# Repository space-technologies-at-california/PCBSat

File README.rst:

=============
PCB Satellite
=============
Space Technologies at Cal (https://stac.berkeley.edu)

University of California, Berkeley

Getting Started
===============
Clone this repository. Then:

Eagle
-----
#. Obtain the `STAC Eagle library <https://github.com/space-technologies-at-california/electronics>`_ by running::
   
    git submodule init
    git submodule update

#. `Add the library to Eagle <https://www.instructables.com/id/Adding-a-Library-to-Eagle-CAD/>`_.

Firmware
--------
#. Install `MSP430-GCC <http://www.ti.com/tool/msp430-gcc-opensource>`_ and
   `MSPDebug <https://dlbeer.co.nz/mspdebug/>`_.

#. In *firmware/*, make a new file called *msp430.mk.inc* and specify the path
   to your MSP430-GCC installation. For example::

    MSP430_TOOLCHAIN=/usr/local/gcc-msp430-ti-toolchain-5.01.02.00

#. Run ``make`` from *firmware/* to build all firmware configurations. To
   build a specific configuration, change to the appropriate subdirectory (for
   example, *debug/*) and run ``make``. If ``make`` complains about a missing
   *gitrev.h*, type ``make gitrev.h`` and re-run.

#. To change a build configuration, edit *config.h* in the appropriate
   subdirectory.

Programming
~~~~~~~~~~~
#. Obtain a programmer. We use the MSP430F5529 LaunchPad to program our sprite
   using Spy-Bi-Wire (SBW), but any SBW-compatible programmer should work.

#. Disconnect the 5V, 3V, GND, SBW RST and TST jumpers from the LaunchPad.

#. Connect the 3V, GND, SBW RST and TST jumpers on the ezFET-lite side to the
   target.

#. Run ``make prog`` to program, and run ``make verify`` to read back what was
   programmed.

Simulation
----------
Dependencies: igrf12 (https://github.com/scivision/igrf12)

#. Run ``python3 pull_iss_locdata.py``. This will collect (timestamp, latitude,longitude) data of the ISS for 9 hours at 10 second increments. This will create an output file in the current directory titled ``iss_loc_data_{timestamp}.csv``.  
#. Run ``python3 data_gen.py -f iss_loc_data_{timestamp}.csv`` where timestamp corresponds to the file created in the previous step. This will create an output file in the current directory that contains magnetometer data (x,y,z), gyrometer data (x,y,z), and the expected axis and power that the PCBSat should rotate along in addition to the file's previous contents. This output file will be titled ``full_{timestamp}.csv``. The units for the magnetometer data are Gauss and the units for the gyrometer data are radians/second.  

The models for predicting power and axis are still in progress. 

To run tensorboard, navigate to /simulations/python/ and execute `tensorboard --logdir="tmp/model/"`. Make sure that you have the most recent versions of tensorflow and tensorboard installed. 

Directory Structure
===================
- ./eagle : Contains all necessary Eagle files for the sprite board

  - ./eagle/sprite-test: Contains the version of the sprite manufacture by 
    Bay Area Circuits as a test board. It is largely based on the sprite
    verison created by Zac Manchester here: https://github.com/kicksat/sprite

  - ./eagle/final-sprite: Contains the version of the sprite we are currently
    working on. Our sprite began from the attitude-sprite designed by Zac
    Mancherster here: https://github.com/kicksat/attitude-sprite

  - ./eagle/electronics: STAC Eagle library submodule. See Eagle_. Please add
    any parts to the stac.lbr file contained there.
    
- ./simulation : Contains all the simulation netlists and other data 

- ./firmware : Contains all the firmware for the sprite

- ./gerbers : Contains the gerbers for the sprites. 

`Getting Started with Sprite Development Kit <https://github.com/kicksat/sprite/wiki/Getting-started-with-the-Sprite-Development-Kit>`_

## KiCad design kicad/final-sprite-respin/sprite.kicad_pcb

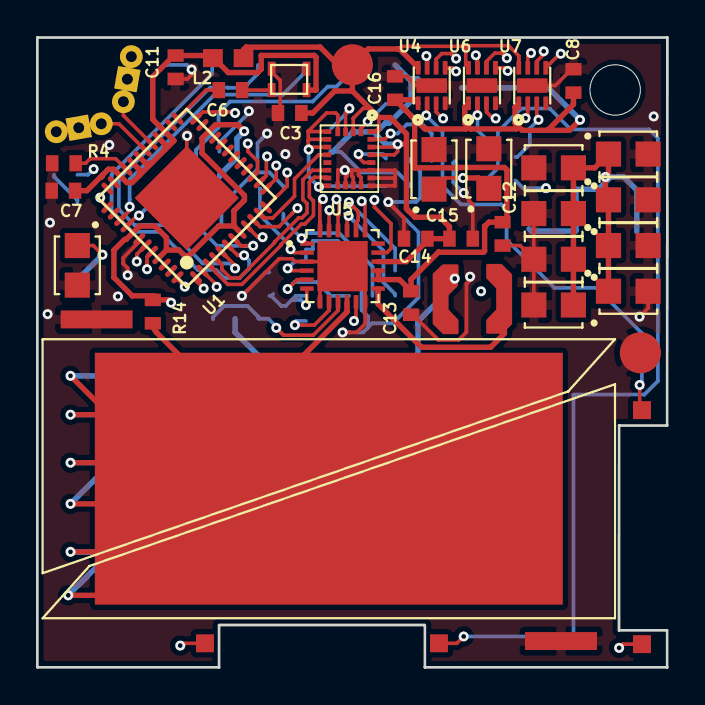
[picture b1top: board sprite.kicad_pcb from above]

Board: 4 copper layers, 35.0 x 35.0 mm, 75 parts (0 on the bottom side), 54 nets.

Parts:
A1, A2: SPRITEANTENNA_ANTENNA
C1, C7: 470n; C0402
C2: 2.2n; C0402
C3, C5, C15: 0.1u; C0402
C4, C6, C9, C11: 10n; C0402
C8, C12, C16, C17: 10u; C0402
C10, C18, C19, C20, C21, C22, C23, C24, C25, C26, C27, C28, C29, C30, C31, C32, C33: CPH3225A; CAPCP3225X100N
C13, C14: 4.7u; C0402
J1: M20-7910442R
L1: LPS4018-223M
L2: 12 nH; 0603
L3, L4: PCBSAT-TORQUECOIL
LED1: LED0603; LED-0603
MK1: Mounting_Hole
R1: 43K; R0402
R2: 270R; R0402
R3, R5, R6: 10K; R0402
R4: 56K; R0402
R7: 150K; R0402
R8: 1M; R0402
R9: 7K; R0402
R10: 200k; R0402
R11, R12, R22: 15R; R0402
R13, R14: OPT; R0402
R15: 5.49M; R0402
R16: 453K; R0402
R17: 4.53M; R0402
R18, R19: 5M; R0402
R20: 4.42M; R0402
R21: 5.6M; R0402
U1: CC430F513X; TI_MSP430_V16_RGZ48
U2: LSM9DS1; LGA24-8X4
U3: SPRITETCXO_TCXO_7Z; SPRITETCXO_TXC_7Z
U4, U6, U7: DRV8837; SON50P200X200X75-8N
U5: ADP5092; QFN50P400X400X100-25N
U8, U9: TASC
X1, X2: SPRITEPIN_SPRITE_PIN

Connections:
/DRDY: U1.11, U2.9
/DSW: U1.24, U5.22
/EN_1: U1.43, U4.7
/EN_2: U1.44, U6.7
/EN_3: U1.48, U7.7
/INT1: U1.4, U2.11
/INT2: U1.3, U2.12
/PGOOD: U1.12, U5.19
/PWM1: U1.1, U4.6, U6.6, U7.6
/PWM2: U1.2, U4.5, U6.5, U7.5
/REF: R15.2, R18.2, R20.2, U5.1
/REGGOOD: U1.37, U5.11
/REG_D0: U1.13, U5.24
/REG_D1: U1.15, U5.23
/RF_N: A1.IN1, A1.IN2, A1.IN3, U1.30
/RF_P: A2.IN1, A2.IN2, A2.IN3, U1.29
/SCL: R3.2, U1.9, U2.2
/SDA: R5.2, U1.10, U2.4
/SETHYS: R16.1, R17.2, U5.6
/SETPG: R15.1, R16.2, U5.5
/SETSD: R18.1, R19.2, U5.2
/SPIRAL: R22.1, U7.2
/SWN: L1.P$2, U5.13
/TERM: R20.1, R21.2, U5.4
/TST: J1.3, U1.39
/UART_RX: J1.5, U1.6
/UART_TX: J1.4, U1.5
/VBAT: C10.1, C18.1, C19.1, C20.1, C21.1, C22.1, C23.1, C24.1, C25.1, C26.1, C27.1, C28.1, C29.1, C30.1, C31.1, C32.1, C33.1, U5.17
/VCORE: C1.1, U1.7
/~RST: C2.2, J1.2, R1.2, U1.40
GND: C1.2, C2.1, C3.2, C4.2, C5.2, C7.2, C8.2, C9.2, C10.2, C11.2, C12.2, C13.2, C14.2, C15.2, C16.2, C17.2, C18.2, C19.2, C20.2, C21.2, C22.2, C23.2, C24.2, C25.2, C26.2, C27.2, C28.2, C29.2, C30.2, C31.2, C32.2, C33.2, J1.6, LED1.C, R4.2, R8.1, R9.2, R10.1, R17.1, R19.1, R21.1, U1.42, U1.TP, U2.14, U2.15, U2.16, U2.17, U2.18, U2.19, U2.20, U3.GND1, U3.GND2, U4.4, U4.9, U5.3, U5.7, U5.12, U5.25, U6.4, U6.9, U7.4, U7.9, U8.MINUS1, U8.MINUS2, U9.MINUS1, U9.MINUS2, X2.PIN
unnamed: C4.1, U2.21
unnamed: C5.1, U2.24
unnamed: C6.1, U1.25
unnamed: C6.2, U3.OUT
unnamed: C9.1, U5.8
unnamed: L3.1, U4.3
unnamed: L3.2, R11.2
unnamed: L4.1, R12.2
unnamed: L4.2, U6.3
unnamed: LED1.A, R2.2
unnamed: R2.1, U1.14
unnamed: R4.1, U1.33
unnamed: R6.2, U2.5, U2.6, U2.7, U2.8, U2.13
unnamed: R7.1, R8.2, U5.9
unnamed: R9.1, U5.20
unnamed: R10.2, U5.21
unnamed: R11.1, U4.2
unnamed: R12.1, U6.2
unnamed: R22.2, U7.3
VCC: C3.1, C14.1, C15.1, J1.1, L2.1, R1.1, R3.1, R5.1, R6.1, R13.2, R14.1, U1.8, U1.22, U1.41, U1.45, U2.1, U2.3, U2.22, U2.23, U4.8, U5.16, U6.8, U7.8, X1.PIN
VCCA: C7.1, C11.1, L2.2, U1.27, U1.28, U1.31, U1.32, U1.34, U3.VCC
VCCINT: C17.1, L1.P$1, R7.2, R14.2, U5.10, U8.PLUS, U9.PLUS
VCCIO: C8.1, C12.1, C13.1, C16.1, R13.1, U4.1, U5.14, U5.15, U6.1, U7.1

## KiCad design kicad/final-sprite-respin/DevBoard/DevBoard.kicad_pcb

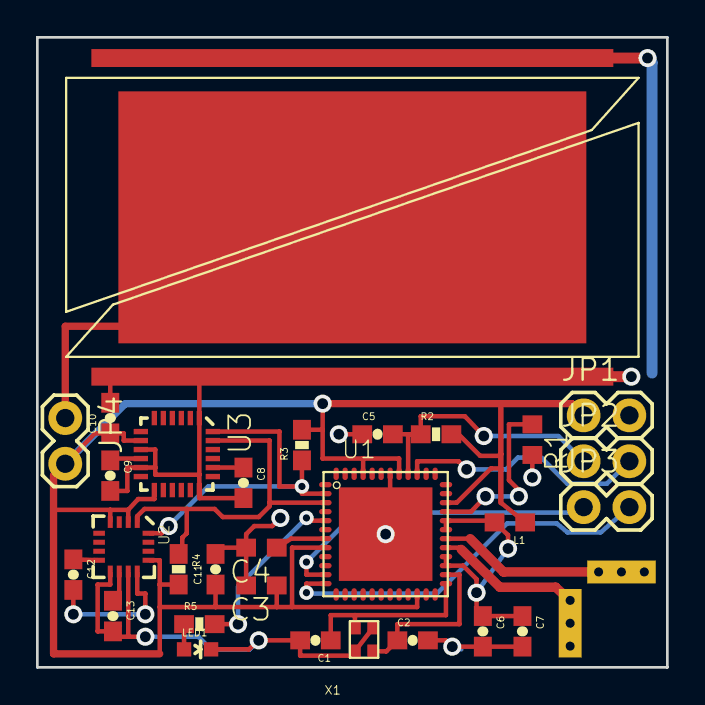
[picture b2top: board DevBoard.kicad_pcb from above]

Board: 16 copper layers, 35.0 x 35.0 mm, 31 parts (0 on the bottom side), 23 nets.

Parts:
ANT-N1: ANTENNA
ANT-P1: ANTENNA
C1, C2: 27pF; 0603-CAP
C3, C4: 470nF; C0603
C5, C8: 2.2nF; 0603-CAP
C6, C9, C11: 100nF; 0603-CAP
C7, C10: 10nF; 0603-CAP
C12: 220nF; 0603-CAP
C13: 4.7uF; 0603-CAP
JP1, JP2, JP3, JP4: M02PTH; 1X02
L1: 12 nH; 0603
LED1: LED0603; LED-0603
R1: 56K; R0603
R2: 47K; 0603-RES
R3, R4: 4.7K; 0603-RES
R5: 270R; 0603-RES
S1: TASC
U1: CC430F5137; RGZ48
U2: HMC5883LSMD; 16LPCC
U3: ITG-3200; QFN-24
X1: 26 MHz; ABM11_CERAMIC-SMD-CRYSTAL

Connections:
/SCL: R4.1, U1.3, U2.1, U3.23
/SDA: R3.1, U1.2, U2.16, U3.24
GND: C1.2, C2.2, C3.2, C4.2, C5.1, C6.2, C7.2, C8.2, C9.2, C10.2, C11.2, C13.2, JP1.2, LED1.C, R1.2, S1.MINUS1, S1.MINUS2, U1.42, U1.TP, U2.9, U2.11, U3.1, U3.9, U3.11, U3.18, X1.P$2, X1.P$4
unnamed: ANT-N1.IN1, ANT-N1.IN2, ANT-N1.IN3, U1.30
unnamed: ANT-P1.IN1, ANT-P1.IN2, ANT-P1.IN3, U1.29
unnamed: C1.1, U1.25, X1.P$1
unnamed: C2.1, U1.26, X1.P$3
unnamed: C4.1, U1.7
unnamed: C5.2, JP2.1, R2.1, U1.40
unnamed: C6.1, C7.1, L1.2, U1.27, U1.28, U1.31, U1.32
unnamed: C8.1, U3.20
unnamed: C9.1, U3.10
unnamed: C12.1, U2.8
unnamed: C12.2, U2.12
unnamed: C13.1, U2.10
unnamed: JP2.2, U1.39
unnamed: JP3.1, U1.11
unnamed: JP3.2, U1.12
unnamed: JP4.1, S1.PLUS
unnamed: LED1.A, R5.1
unnamed: R1.1, U1.33
unnamed: R5.2, U1.5
VCC: C3.1, C10.1, C11.1, JP1.1, JP4.2, L1.1, R2.2, R3.2, R4.2, U1.8, U1.22, U1.34, U1.41, U1.45, U2.2, U2.4, U2.13, U3.8, U3.13

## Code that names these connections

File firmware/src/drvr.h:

#pragma once

#include "lsm.h"

enum Driver {
    XAXIS = 0, // EN_3, Spiral inductor
    YAXIS = 1, // EN_2, Back top
    ZAXIS = 2, // EN_1, Back left
};

uint8_t run_actuation(uint8_t axis, int8_t power, struct vec3_s data[static 1]);
void setup_pwm(void);

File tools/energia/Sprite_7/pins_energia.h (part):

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	P1,		     /*  4 - P1.7 */
	P1,          /*  5 - P1.6 */
	P1,          /*  6 - P1.5 */
	NOT_A_PIN,   /*  7 - VCORE */
	NOT_A_PIN,   /*  8 - DVCC */
	P1,          /*  9 - P1.4 */
	P1,          /* 10 - P1.3 */
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	NOT_A_PIN,   /* 26 - RF_XOUT */
	NOT_A_PIN,   /* 27 - AVCC_RF */
	NOT_A_PIN,   /* 28 - AVCC_RF */
	NOT_A_PIN,   /* 29 - RF_P */
	NOT_A_PIN,   /* 30 - RF_N */
	NOT_A_PIN,   /* 31 - AVCC_RF */
	NOT_A_PIN,   /* 32 - AVCC_RF */
	NOT_A_PIN,   /* 33 - R_BIAS */
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	BV(7),	     /*  4 - P1.7 */
	BV(6),       /*  5 - P1.6 */
	BV(5),       /*  6 - P1.5 */
	NOT_A_PIN,   /*  7 - VCORE */
	NOT_A_PIN,   /*  8 - DVCC */
	BV(4),       /*  9 - P1.4 */
	BV(3),       /* 10 - P1.3 */
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	NOT_A_PIN,   /* 26 - RF_XOUT */
	NOT_A_PIN,   /* 27 - AVCC_RF */
	NOT_A_PIN,   /* 28 - AVCC_RF */
	NOT_A_PIN,   /* 29 - RF_P */
	NOT_A_PIN,   /* 30 - RF_N */
	NOT_A_PIN,   /* 31 - AVCC_RF */
	NOT_A_PIN,   /* 32 - AVCC_RF */
	NOT_A_PIN,   /* 33 - R_BIAS */
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
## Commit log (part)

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2018-06-10 bump library version
2018-06-10 started layout and fixed R0402 packages
2018-06-10 some schematic updates
2018-06-11 Placed all components, probably
2018-06-11 hand routed RF_P and RF_N
2018-06-11 updated drc rules
2018-06-11 Eagle autoroute with buried and 2 blind
2018-06-11 did most of the long traces
2018-06-11 more stuff done
2018-06-11 routed some more routes
2018-06-12 more stuff finished
2018-06-13 Add straight edge RS solar cell drawing
2018-06-13 Move dev board model
2018-06-13 moved all 3 drivers to the bottom side, removed the need for using interlayers and decreased the total number of vias
2018-06-13 added new trisol footprint to layout
2018-06-14 Finishing up more of the Layout
2018-06-16 Fix inductor
2018-06-16 Remove extra test point
2018-06-16 Clean up traces
2018-06-17 Fix footprints and layout
2018-06-17 More routing, removed some vias from the bottom layer
2018-06-17 spiral inductor that can actually be fab'd
2018-06-17 more routes fixed, removed some vias
2018-06-17 Fixing pgood renaming
2018-06-17 Fix TrisolX solar cell courtyard
2018-06-17 Remove pours over PCB inductor
2018-06-17 Add logo
2018-06-17 Add production files
2018-06-18 Changed resistor values
2018-06-18 updated resistitator values again
2018-06-18 Import TI RF example
2018-06-18 Import MSPGCC toolchain
2018-06-18 Adding Zac's libraries
2018-06-18 added spice decks for solar cell simulation
2018-06-18 Add blinky LED
2018-06-18 Remove extra copy of blink
2018-06-18 Add CXX macro
2018-06-18 Add msp430.mk.inc and update README
2018-06-19 Move RF example
2018-06-19 Remove old Energia libraries
2018-06-20 Build RadioBeacon
2018-06-27 Change submodule URL
2018-06-27 Support GNU Make 3.82
    macOS has an old version of GNU Make that does not support shell
    expansion assignment via '!='. Consequently, fall back to the least
    common denominator and break compatibility with other Make's.
2018-06-27 Rename entry point to sprite_main
2018-06-27 Replace sprite_main with RadioData example
2018-06-27 Add note about tenting vias
2018-06-29 Improve blink example
2018-06-29 Update schematic title block matter
2018-06-29 Re-center schematic
2018-06-29 Update values from schematic
2018-06-29 Update fab drawing
2018-06-30 Update blink for new board
2018-07-01 Track core fixes needed for sprite_main to work
2018-07-01 Blink twice before transmitting
2018-07-01 Use SYSTEM_CLK_FREQ
2018-07-01 Bring up UART
2018-07-01 Include Git revision
2018-07-01 Add Wire library
2018-07-01 Fix gitrev.h build
2018-07-01 simple lsm code
2018-07-01 sprite pwm updated
2018-07-01 updating all the submodules to clean up git
2018-07-01 some updates to pins.h
2018-07-01 Add ground vias
2018-07-01 Fix inductor test points
2018-07-01 Add linker flags to GC sections
2018-07-02 Fix size of R10
2018-07-02 Reduce solar cell rectangle size
2018-07-02 Bump revision
2018-07-02 Add STAC decals
2018-07-02 did some nephew tier routing, but added optional 0ohm resistor between Pgood and RST
2018-07-04 explicitly set REGD0 and REGD1 low
2018-07-04 moved stuff around
2018-07-05 fixed makefile
2018-07-05 preliminary add of pins.c and pwm.c
2018-07-05 more pins stuff, some pwm stuff
2018-07-05 main modifications
2018-07-05 fixed compilation issues part 2
2018-07-05 removed old pwm cpp file
2018-07-05 added i2c code
2018-07-05 fixing broken pins.h file
2018-07-05 fixed merge issues
2018-07-06 making makefile also remove generated .map file
2018-07-06 Port radio firmware to C
2018-07-06 Update right gitignore
2018-07-06 added cc430 uart code
2018-07-06 Add deep_sleep() and blink LED with LPM4
2018-07-06 Reorganize
2018-07-06 Fix permissions
2018-07-06 Replace delayMicroseconds() with LPM0 sleep
2018-07-06 Fix use of uninitialized variable
2018-07-06 Blink twice on power up
2018-07-06 Move HPRM to main and radio init to radio_init()
2018-07-06 Initialize radio
2018-07-06 Do not change MCLK frequency
2018-07-06 Declare radio-only functions static
2018-07-06 Add prototypes for main.c
2018-07-06 Re-add delay between bytes
2018-07-08 uart code that doesn't work
2018-07-08 minor modifications to i2c but still not workign
2018-07-09 Move UART and LSM init functions out of init_core()
2018-07-09 fixed F_CPU
2018-07-09 Set GIE in init_core()
2018-07-09 Add power check and interrupts
2018-07-10 Blink LED on UART only when DEBUG_UART is set
2018-07-10 Give FLL time to settle
    This was causing problems with UART right after startup.
2018-07-10 Print gitrev to UART
2018-07-11 Sort includes
2018-07-11 Add state variable in .infoB
2018-07-11 Count number of power cycles
2018-07-11 Use struct missioninfo
2018-07-11 Use sizeof(struct missioninfo)
2018-07-12 Update uart print statements
2018-07-12 removed useless stuff from pins.c and pins.h
2018-07-14 Add state machine mechanics
2018-07-15 Add missing include
2018-07-15 Cast pointers
2018-07-15 test code for flash writes
2018-07-16 Flash next state before running state_main()
2018-07-22 Fixed i2c and lsm transactions
2018-07-22 Declare uart_write* functions const
2018-07-22 Clean up LSM data printing
2018-07-22 initial version of battery code
2018-07-22 Repudiate main_flash()
2018-07-22 Add new flash state recorder
2018-07-23 Changed magnetometer mode for ADC
2018-07-29 adc code
2018-07-30 Add missing ref.h
2018-07-31 Add radio power flag handling
2018-07-31 Pick up only *.c files
2018-07-31 Fixes for lsm interrupt based polling
2018-07-31 Build with DEBUG set
2018-07-31 Move run_* functions to respective source files
2018-07-31 Set interrupts correctly
2018-07-31 Enable interrupts for LSM
2018-08-01 Cosmetic cleanup
2018-08-01 Add preliminary driver control
2018-08-05 switching to using SMCLK
2018-08-05 Turn on regulator
2018-08-05 Fix driver test code
2018-08-09 python code folder initial commit
2018-08-12 Add preliminary interface to mission planner
2018-08-16 Remove legacy
2018-08-18 Update radio register comments
    While here, remove the ones that we didn't check and potentially
    misleading ones. Better to check against datasheet and add them back
    when we need them.
2018-08-23 Save supercap footprint in sprite library
2018-08-23 Dump in a few more supercaps
2018-08-24 added more caps and moved a couple traces
2018-08-24 routes fixed, no DRC violations, 11 new caps
2018-08-24 umac cutout spot
2018-08-24 moving some passives
2018-08-25 fixed silkscreen
2018-08-25 Flipped umac pads
2018-08-25 Flipped umac pads again...stupid avi
2018-08-25 WIP routing w slot
2018-08-25 Added edge cut. Final version probably
2018-08-25 Remove old Engeria support files
2018-08-25 Remove silkscreen logo on back
2018-08-25 Line up slot on grid
2018-08-25 Remove back silkscreen logo
2018-08-25 Promote gitignore
2018-08-25 Add more slot margin and move top logo
2018-08-25 Fix unconnected
2018-09-03 Add PRNs from Zac verbatim
2018-09-09 fixing lsm issue by resetting lsm at every call to setup()
2018-09-09 Add flight PRNs
2018-09-09 Move PRN to separate file
2018-09-10 Run LSM setup only once
2018-09-10 fixing lsm magnetometer code, by reseting the ctrl_reg3_m
2018-09-10 Stop rebooting XL
2018-09-10 Use reasonable data types
2018-09-10 Nail down argument
2018-09-10 Stop rebooting magnetometer
2018-09-10 Add missing ref.c
2018-09-10 Clean up header
2018-09-11 add magnetorquer .py file
2018-09-11 Move to correct location
2018-09-11 updates to drv code
2018-09-11 updates to drvr.c
2018-09-12 Hook in battery monitor
2018-09-12 Remove executable bits
2018-09-12 Document batt_voltage
2018-09-12 Check for MPPT failure
    Report inconsistencies between PGOOD and measured battery voltage.
2018-09-12 Stop doing a stupid division
2018-09-12 Stop header file abuse
2018-09-12 Fix warnings
2018-09-12 Remove unused files
2018-09-12 Clean up unused symbols
2018-09-12 Enable WDT
2018-09-12 Pet watchdog
2018-09-12 Document transmission time
2018-09-12 updated battery monitor to also measure and store temperature
2018-09-12 updated lsm code, useless change to drvr only to pull changes
2018-09-12 making drvr functions local
2018-09-12 Add random delay between transmissions
2018-09-12 Keep track of timing through long sleeps
2018-09-12 Make rand_int() function
2018-09-12 Construct message
2018-09-12 added lsm code to find angular acceleration
2018-09-12 Add missing ifdef
2018-09-12 Fix warning
2018-09-12 Separate debug PRN from debug build
2018-09-12 Adjust timing
2018-09-12 updates to blocking lsm and blocking drvr
2018-09-12 fixing compilation issues
2018-09-12 adding final transmit stuff
2018-09-12 Do not attempt to actuate if LSM setup fails
2018-09-13 Flip UMAC connectors and offset coil pad
2018-09-13 Change solder paste
2018-09-13 Add supercap to shared library
2018-09-13 Remove duplicated library
2018-09-13 Point to moved footprint library
2018-09-14 Don't turn off ADC and temp sensor on startup
2018-09-14 Reorder init code
2018-09-14 Make tx_msg global
2018-09-14 Document interrupt clear
2018-09-14 Harden power check
2018-09-14 fixing norm function
2018-09-14 Fix redundant pin setup
2018-09-14 Set GPF if ADC setup fails
2018-09-14 Minor changes to battery monitor
2018-09-14 Make radio use globals
2018-09-14 Remove via-in-pad
2018-09-15 Cap board respin for thinner profile
2018-09-15 Cap board repsin with all nets connected
2018-09-15 Add via to fix layer 3 fill
    While here connect antenna pins to silence unconnected warning.
2018-09-16 moving around traces to create room for the center spiral inductor
2018-09-16 Prepare layout for spiral inductor
2018-09-16 adding proportional bdot control
2018-09-17 updated controller
2018-09-17 fixing some compilation issues
2018-09-17 Route spiral inductor
2018-09-17 updated pcb with spots for 6 more caps
2018-09-17 Adjust silkscreen text and courtyard width
2018-09-17 Clean up silkscreen
2018-09-17 final version
2018-09-17 setup magnetorquer_out in lsm.h
2018-09-18 fixed lsm.h and fixed incorrect directory for firmware download
2018-09-19 Fix edge cut
2018-09-23 added TODOs
2018-09-24 Only operate radio in safe mode
2018-09-24 Reorganize directory structure
2018-09-24 Track dependencies
2018-09-24 Add controller debugging outputs
2018-09-24 Print data output for debug
2018-09-25 Add delay between transmissions
2018-09-25 updated python controller
2018-09-25 fixed dot product
2018-09-25 Split calculations to separate source file
2018-09-25 testing - dont fly
2018-09-26 u int tests
2018-09-26 added testing
2018-09-26 fixed printing
2018-09-26 fixed some values and cleaned up code
2018-10-11 Fixed moving_average fn in calc.c
2018-10-12 Move MOVING_AVG_FILTER_LEN definition
2018-10-12 Add moving average test
2018-10-12 Optimize
2018-10-12 Flip GPF and SAFEMODE bit
    Only the bottom 6 bits of 'faults' get transmitted. GPF is less
    important than SAFEMODE.
2018-10-12 added firmware code on new branch for no torque board - sends mag and gyro data in last 2 bytes
2018-10-12 changed m_data and meas_alpha to int16 - should be 9 bytes now - maybe update char tx_msg
2018-10-13 Add two PRNs
2018-10-13 Remove state recorder
2018-10-14 Update power setting
2018-10-14 Add build configurations for S1-S5
2018-10-14 Correctly include config.h
2018-10-14 Add convenience programming script
2018-10-14 Add Sprite 7
2018-10-14 Remove admonition
2018-10-14 Move norm function
2018-10-14 Add norm test
2018-10-14 Fix conflicting definition
2018-12-19 Initial version of data gen for tf experiments
2018-12-20 updated tf_data_gen
2018-12-21 updated generating g_data
2018-12-21 Created script iss_loc.py that will generate 10800 seconds (3 hours) of timestamp, latitude, longitude data
2018-12-21 Ran iss_loc.py script for 9 hours and stored data into iss_loc_data_1545365126.csv. iss_loc_data_1545364972.csv is just a test file
2018-12-21 added constant gyro data
2018-12-21 Update README.rst
    Added information about new simulation data creation scripts
2018-12-23 Update README.rst
    consolidated data generation files
2018-12-23 Changed gyro data to be in radians/s instead of deg/s
2019-01-01 added method for unique random init of gyro data - still axis=1 issue
2019-01-01 Added offset to mag_x. Full_ files have gyro data that is the same for all rows. fullunique_ files have gyro data that is unique to each row.
2019-01-03 Added prediction output to compare against truth and save models within model_dir location for use in tensorboard
2019-01-13 updated power and axis model
2019-01-28 tested torque
2019-01-28 added note on time that we need to fix
2019-02-18 KRR implemented

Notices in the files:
tools/energia/Sprite_7/pins_energia.h:
Copyright (c) 2012 Robert Wessels. All right reserved.
Copyright (c) 2007 David A. Mellis
Public License along with this library; if not, write to the
Free Software Foundation, Inc., 59 Temple Place, Suite 330,
Boston, MA  02111-1307  USA
